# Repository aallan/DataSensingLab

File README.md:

This repository contains code and hardware designs for several different boards associated with the [Data Sensing Lab](http://datasensinglab.com) project.

##Google I/O

Here you can find the code and hardware designs for the sensor motes used by the [Data Sensing Lab](http://datasensinglab.com) at Google I/O in 2013. Details of the previous generation of motes, used at the O'Reilly Strata conferences have their [own repository](https://github.com/aallan/SensorMote). You can now [buy these boards](http://datasensinglab.com/dslstore/) at the Lab Store.

##Data Sensing Lab Workshops

The code and hardware designs for the Data Sensing Lab Arduino Shield, used as part of the Workshop kit, and associated with the "[Distributed Network Data](http://www.anrdoezrs.net/click-6760607-11260198?url=http%3A%2F%2Fshop.oreilly.com%2Fproduct%2F0636920028802.do%3Fcmp%3Daf-strata-book-product_cj_9781449360269_%25zp&cjsku=0636920028802)" workshop run by Data Sensing Lab fellows Alasdair Allan and Kipp Bradford.

##Distributed Network Data

The code and hardware designs for the for the shield board associated with the "[Distributed Network Data](http://www.anrdoezrs.net/click-6760607-11260198?url=http%3A%2F%2Fshop.oreilly.com%2Fproduct%2F0636920028802.do%3Fcmp%3Daf-strata-book-product_cj_9781449360269_%25zp&cjsku=0636920028802)" book written by Data Sensing Lab fellows Alasdair Allan and Kipp Bradford.

##Strata CA, 2013

The Sensor Mote from Strata Conference in California in 2013

*Note:* Before you can open the [Fritzing](http://fritzing.org/) (.fzz) file—depending on which version of Fritzing you have—you may need to install the [Adafruit Fritzing Library](https://github.com/adafruit/Fritzing-Library). A full [Bill of Materials](https://docs.google.com/spreadsheet/pub?key=0AugbBYkicsD0dGE2TFZxSi1pV0dEalZ0ZVpvWkNHclE&output=html) is also available.

##Strata New York, 2012

The Sensor Mote from the Strata Conference in New York in 2012.

*Note:* Before you can open the [Fritzing](http://fritzing.org/) (.fzz) file—depending on which version of Fritzing you have—you may need to install the [Adafruit Fritzing Library](https://github.com/adafruit/Fritzing-Library). A full [Bill of Materials](https://docs.google.com/spreadsheet/pub?key=0AugbBYkicsD0dGE2TFZxSi1pV0dEalZ0ZVpvWkNHclE&output=html) is also available.

##Enclosures

To 3D-print your own enclosures for the sensor motes, you can download the STL files designed by Brian Jepson of Maker Media.

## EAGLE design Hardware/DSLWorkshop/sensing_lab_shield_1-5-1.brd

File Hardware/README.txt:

README

SensorMote/
    EAGLE files for the SensorMote which was used at Google I/O 2013.

DistributedNetworkData/
    Gerber files for the board associated with the "Distributed Network Data" book 
    by Alasdair Allan and Kipp Bradford.

DSLWorkshop/
    EAGLE files for the PCB used in the DSL Workshop kit, associated with the 
    "Distributed Network Data" workshop by Alasdair Allan and Kipp Bradford.

StrataNY2012/
    Fritzing file for the boards used at Strata New York in 2012.

StrataCA2013/
    Fritizing file for the boards introduced at Strata CA in 2013.

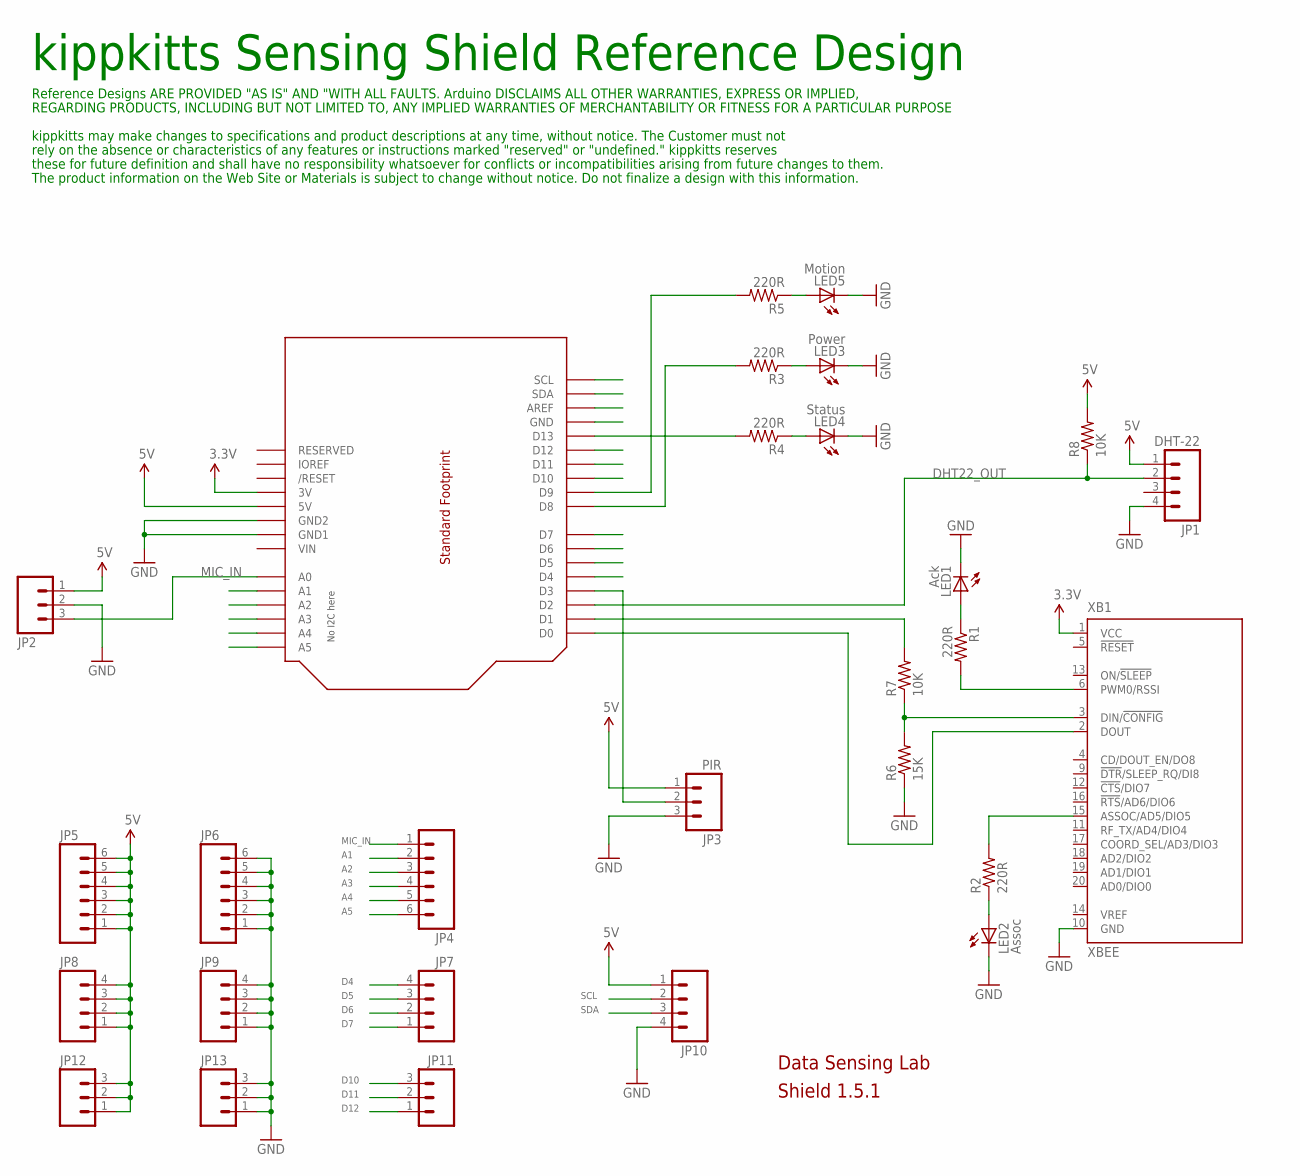
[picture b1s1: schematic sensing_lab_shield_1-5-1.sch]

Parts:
JP1: DHT-22; 1X04
JP2: M03POLAR_LOCK; MOLEX-1X3_LOCK
JP3: PIR; SCREWTERMINAL-3.5MM-3_LOCK.007S
JP4, JP5, JP6: M06SIP; 1X06
JP7, JP8, JP9, JP10: M04PTH; 1X04
JP11, JP12, JP13: M03PTH; 1X03
LED1: Ack; LED3MM
LED2: Assoc; LED3MM
LED3: Power; LED3MM
LED4: Status; LED3MM
LED5: Motion; LED3MM
R1, R2, R3, R4, R5: 220R; 0207/10
R6: 15K; 0207/10
R7, R8: 10K; 0207/10
U1: ARDUINOR3-DIMENSION; ARDUINOR3
XB1: XBEE

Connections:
3.3V: U1.3V, XB1.1 (VCC)
3V3_ARD_TX: R6.2, R7.1, XB1.3 (DIN/!CONFIG)
5V: JP1.1, JP2.1, JP3.1, JP5.1, JP5.2, JP5.3, JP5.4, JP5.5, JP5.6, JP8.1, JP8.2, JP8.3, JP8.4, JP10.1, JP12.1, JP12.2, JP12.3, R8.2, U1.5V
A1: JP4.2, U1.A1
A2: JP4.3, U1.A2
A3: JP4.4, U1.A3
A4: JP4.5, U1.A4
A5: JP4.6, U1.A5
ARD_RX: U1.D0, XB1.2 (DOUT)
ARD_TX: R7.2, U1.D1
D4: JP7.4, U1.D4
D5: JP7.3, U1.D5
D6: JP7.2, U1.D6
D7: JP7.1, U1.D7
D10: JP11.3, U1.D10
D11: JP11.2, U1.D11
D12: JP11.1, U1.D12
DHT22_OUT: JP1.2, R8.1, U1.D2
GND: JP1.4, JP2.2, JP3.3, JP6.1, JP6.2, JP6.3, JP6.4, JP6.5, JP6.6, JP9.1, JP9.2, JP9.3, JP9.4, JP10.4, JP13.1, JP13.2, JP13.3, LED1.K (C), LED2.K (C), LED3.K (C), LED4.K (C), LED5.K (C), R6.1, U1.GND1, U1.GND2, XB1.10 (GND)
MIC_IN: JP2.3, JP4.1, U1.A0
unnamed: LED1.A, R1.1
unnamed: LED2.A, R2.1
unnamed: R1.2, XB1.6 (PWM0/RSSI)
unnamed: R2.2, XB1.15 (ASSOC/AD5/DIO5)
unnamed: LED3.A, R3.1
unnamed: R5.2, U1.D9
unnamed: LED5.A, R5.1
unnamed: R3.2, U1.D8
unnamed: LED4.A, R4.1
unnamed: R4.2, U1.D13
unnamed: JP3.2, U1.D3
SCL: JP10.2, U1.SCL
SDA: JP10.3, U1.SDA
VIN: U1.VIN

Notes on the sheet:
Data Sensing Lab
Shield 1.5.1
kippkitts Sensing Shield Reference Design
Reference Designs ARE PROVIDED "AS IS" AND "WITH ALL FAULTS. Arduino DISCLAIMS ALL OTHER WARRANTIES, EXPRESS OR IMPLIED,
kippkitts may make changes to specifications and product descriptions at any time, without notice. The Customer must not
REGARDING PRODUCTS, INCLUDING BUT NOT LIMITED TO, ANY IMPLIED WARRANTIES OF MERCHANTABILITY OR FITNESS FOR A PARTICULAR PURPOSE
rely on the absence or characteristics of any features or instructions marked "reserved" or "undefined." kippkitts reserves
these for future definition and shall have no responsibility whatsoever for conflicts or incompatibilities arising from future changes to them.
The product information on the Web Site or Materials is subject to change without notice. Do not finalize a design with this information.

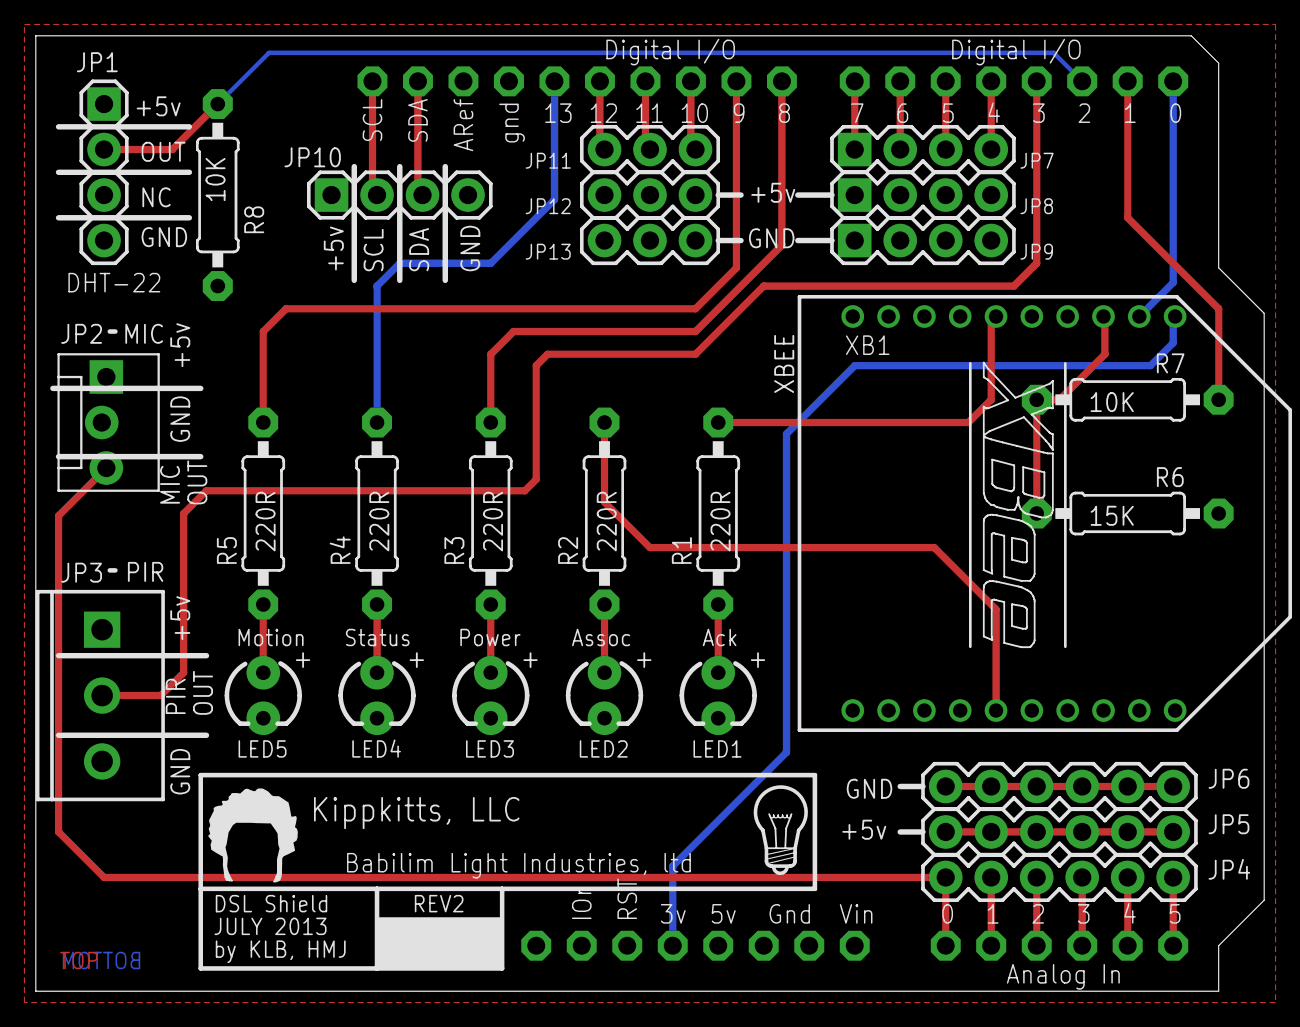
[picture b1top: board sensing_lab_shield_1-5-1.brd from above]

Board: 2 copper layers, 68.6 x 53.3 mm, 30 parts (0 on the bottom side), 33 nets.

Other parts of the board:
U$6: BABILIM_7.5MM
U$7: TOP_DOCU_5MM

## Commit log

2013-08-22 Added images for README.md
2013-08-22 Update LICENSE
2013-09-26 add TSRP as an alternative to XBee
2013-09-26 Added materials for the DSL Shield.
2013-09-26 Textual changes
2013-09-26 Added Strata NY 2012 board
2013-09-26 Updated image
2013-10-20 TSRP updates
2013-10-29 Added another board
2013-10-29 Fixed typo.
2013-10-29 Added a new board.
2014-03-18 Added logo.
2014-03-18 Update README.md
    Added logo.
